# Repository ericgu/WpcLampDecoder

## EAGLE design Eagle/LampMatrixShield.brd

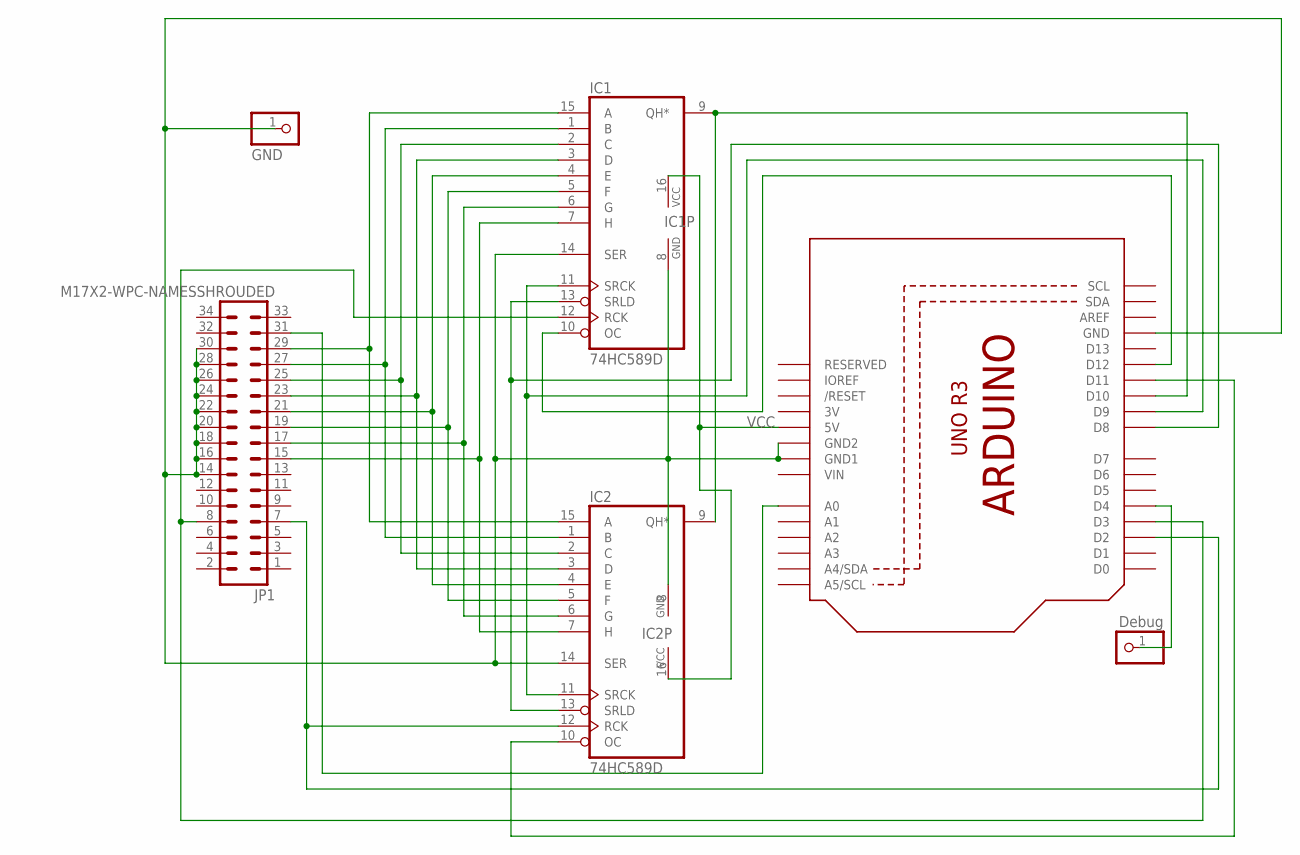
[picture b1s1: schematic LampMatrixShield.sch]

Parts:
IC1, IC2: 74HC589D; SO16
JP1: M17X2-WPC-NAMESSHROUDED; 2X17_SHROUDED
JP2: GND; 1X01-CLEANBIG
JP3: Debug; 1X01-CLEANBIG
U1: ARDUINOR3-BPLACE

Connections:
3V: U1.3V
GND: IC1.8 (GND), IC1.14 (SER), IC2.8 (GND), IC2.14 (SER), JP1.14, JP1.16, JP1.18, JP1.20, JP1.22, JP1.24, JP1.26, JP1.28, JP1.30, JP2.1, U1.GND, U1.GND1, U1.GND2
unnamed: IC1.15 (A), IC2.15 (A), JP1.29
unnamed: IC1.1 (B), IC2.1 (B), JP1.27
unnamed: IC1.2 (C), IC2.2 (C), JP1.25
unnamed: IC1.3 (D), IC2.3 (D), JP1.23
unnamed: IC1.4 (E), IC2.4 (E), JP1.21
unnamed: IC1.5 (F), IC2.5 (F), JP1.19
unnamed: IC1.6 (G), IC2.6 (G), JP1.17
unnamed: IC1.7 (H), IC2.7 (H), JP1.15
unnamed: IC2.12 (RCK), JP1.7, U1.D2
unnamed: IC1.12 (RCK), JP1.8, U1.D3
unnamed: JP1.31, U1.A0
unnamed: IC2.10 (OC), U1.D11
unnamed: IC1.10 (OC), U1.D12
unnamed: IC1.13 (SRLD), IC2.13 (SRLD), U1.D8
unnamed: IC1.11 (SRCK), IC2.11 (SRCK), U1.D9
unnamed: JP3.1, U1.D4
unnamed: IC1.9 (QH*), IC2.9 (QH*), U1.D10
VCC: IC1.16 (VCC), IC2.16 (VCC), U1.5V
VIN: U1.VIN

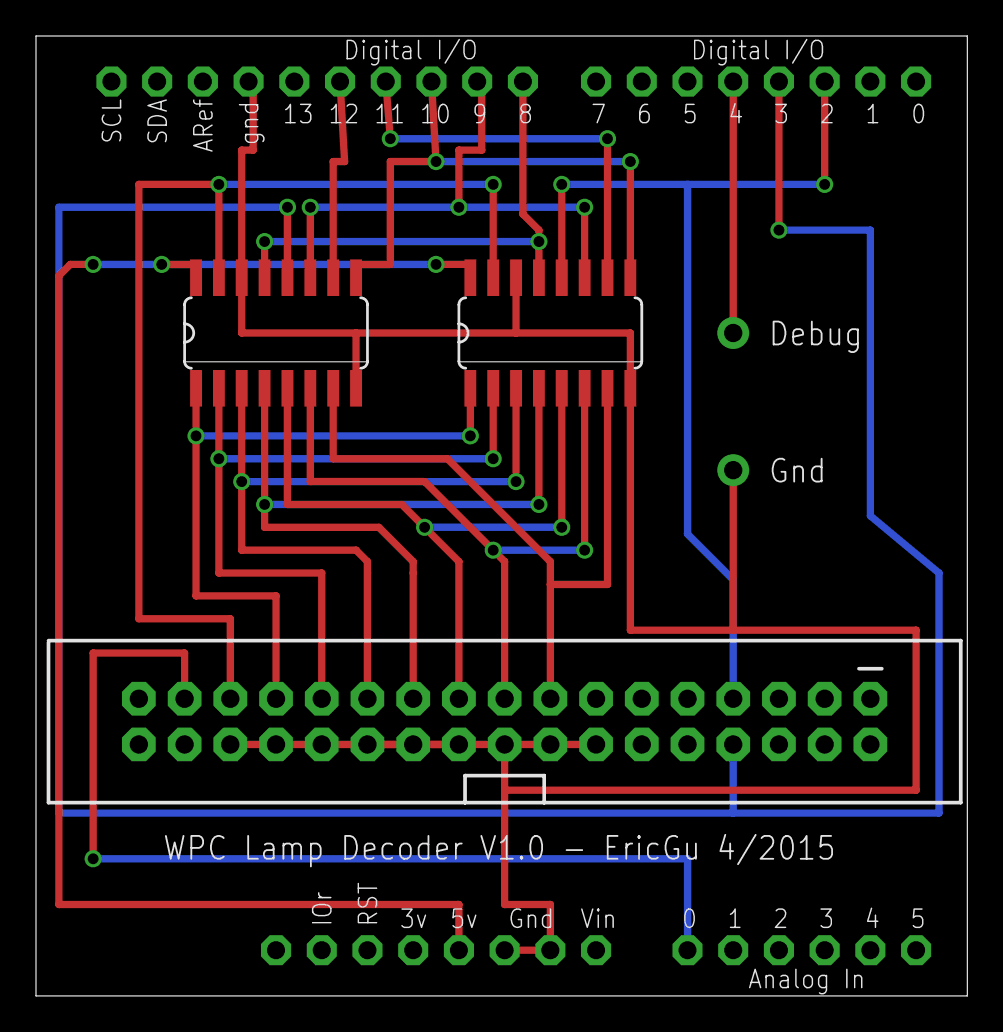
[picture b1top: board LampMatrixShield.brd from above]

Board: 2 copper layers, 51.7 x 53.3 mm, 6 parts (0 on the bottom side), 19 nets.

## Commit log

2019-10-03 Working version
2019-10-03 Eagle files
